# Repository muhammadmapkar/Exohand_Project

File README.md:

# ExoHand

EMG-controlled assistive robotic hand. Built for ECTE351 by Team Orvyn (Group 19).

## Overview

ExoHand reads surface EMG (sEMG) from the forearm, classifies the muscle activity into a hand gesture, and drives four servo-actuated fingers to match. The current system recognizes `rest`, `fist`, and individual-finger gestures (`pinky&ring`, `middle`, `index`, `thumb`), running the trained classifier directly on the microcontroller. VR integration is planned; not yet in this codebase. — see `docs/architecture.md`. Runs the trained classifier on-device (no PC needed for inference).

## EMG-control concept

1. Sample raw EMG at 1 kHz from a single sensor channel.
2. Extract statistical features (MAV, RMS, variance, std dev, waveform length, zero-crossing rate, slope sign changes, skewness, kurtosis, IQR) over a rolling 30-sample window.
3. Classify the window with a Random Forest trained on EMG collected by the team (plus validation against the public NinaPro benchmark dataset).
4. Debounce the result (4 agreeing windows + 150ms hold) before committing to a new gesture.
5. Drive 4 servos through a PCA9685 to match the confirmed gesture, moving smoothly rather than snapping.

Full signal-flow diagram: `docs/architecture.md`.

## Hardware stack

- Teensy 4.0 — main MCU for EMG sampling, feature extraction, and on-device RF inference
- PCA9685 servo driver (I2C, 4 channels)
- MG996R servos (or equivalent)
- SEN0240 EMG sensor
- ESP32-C3, for live telemetry/graph relay (`firmware/current/esp32_bridge.ino` — self-hosted WiFi AP + WebSocket server)

## Repo layout

```
exohand/
├── firmware/        Teensy/ESP32 .ino code — current/ is what's in active use, archive/ is superseded versions
├── web/             static site + the FastAPI live dashboard
├── hardware/        KiCad schematics/PCB, BOM, perfboard build docs
├── signal-processing/  EMG filtering, feature extraction, trained model, datasets
├── docs/            build-log, architecture, decisions, posters
└── media/           screenshots, recordings, concept art
```

Nothing failed or superseded was deleted — old firmware versions, every dated PCB backup, duplicate dataset exports, and earlier notebook runs are all kept under the relevant `archive/` folders. See `docs/build-log.md` for the full story of what was tried and what changed.

## How to build / run

**Firmware:** open `firmware/current/teensy_final.ino` in Arduino IDE with Teensyduino (board: Teensy 4.0), plus the Adafruit PWM Servo Driver and Watchdog_t4 libraries. It includes `ai_classifier_model.h`, which is checked into `firmware/current/` and compiles as-is. To regenerate it from a retrained model, run `python3 signal-processing/export_model_to_header.py` (loads `ExoHand_RF_Model.joblib` + `ExoHand_Scaler.joblib`, writes the header back to `firmware/current/ai_classifier_model.h`).

**Signal processing / training:** `pip install -r signal-processing/requirements.txt`, then `signal-processing/ExoHand_EMG_Classifier_RF_V2.ipynb` to retrain, or `signal-processing/live_predict.py` to run live PC-side inference over serial.

**Live dashboard:** `web/dashboard/app.py` (FastAPI). Install `web/dashboard/requirements.txt`, run with `uvicorn app:app`, open the browser page it serves. Includes a `/api/demo` mode that fakes EMG data if no hardware is connected.

**Website:** `web/website.html` is the current main site (Live Rehab dashboard view, live EMG chart, camera-based sensor-placement assistant). `web/archive/ORVYNUpdated.html` is an earlier, less developed version.

**Hardware:** schematics and PCB in `hardware/schematics/`, BOM in `hardware/bom/`, perfboard wiring/assembly in `hardware/perfboard/`.

## Credit

Team Orvyn (Group 19). My role: led firmware (Teensy), EMG signal processing, hardware build. Data collection was team effort. Benchmark data from NinaPro.

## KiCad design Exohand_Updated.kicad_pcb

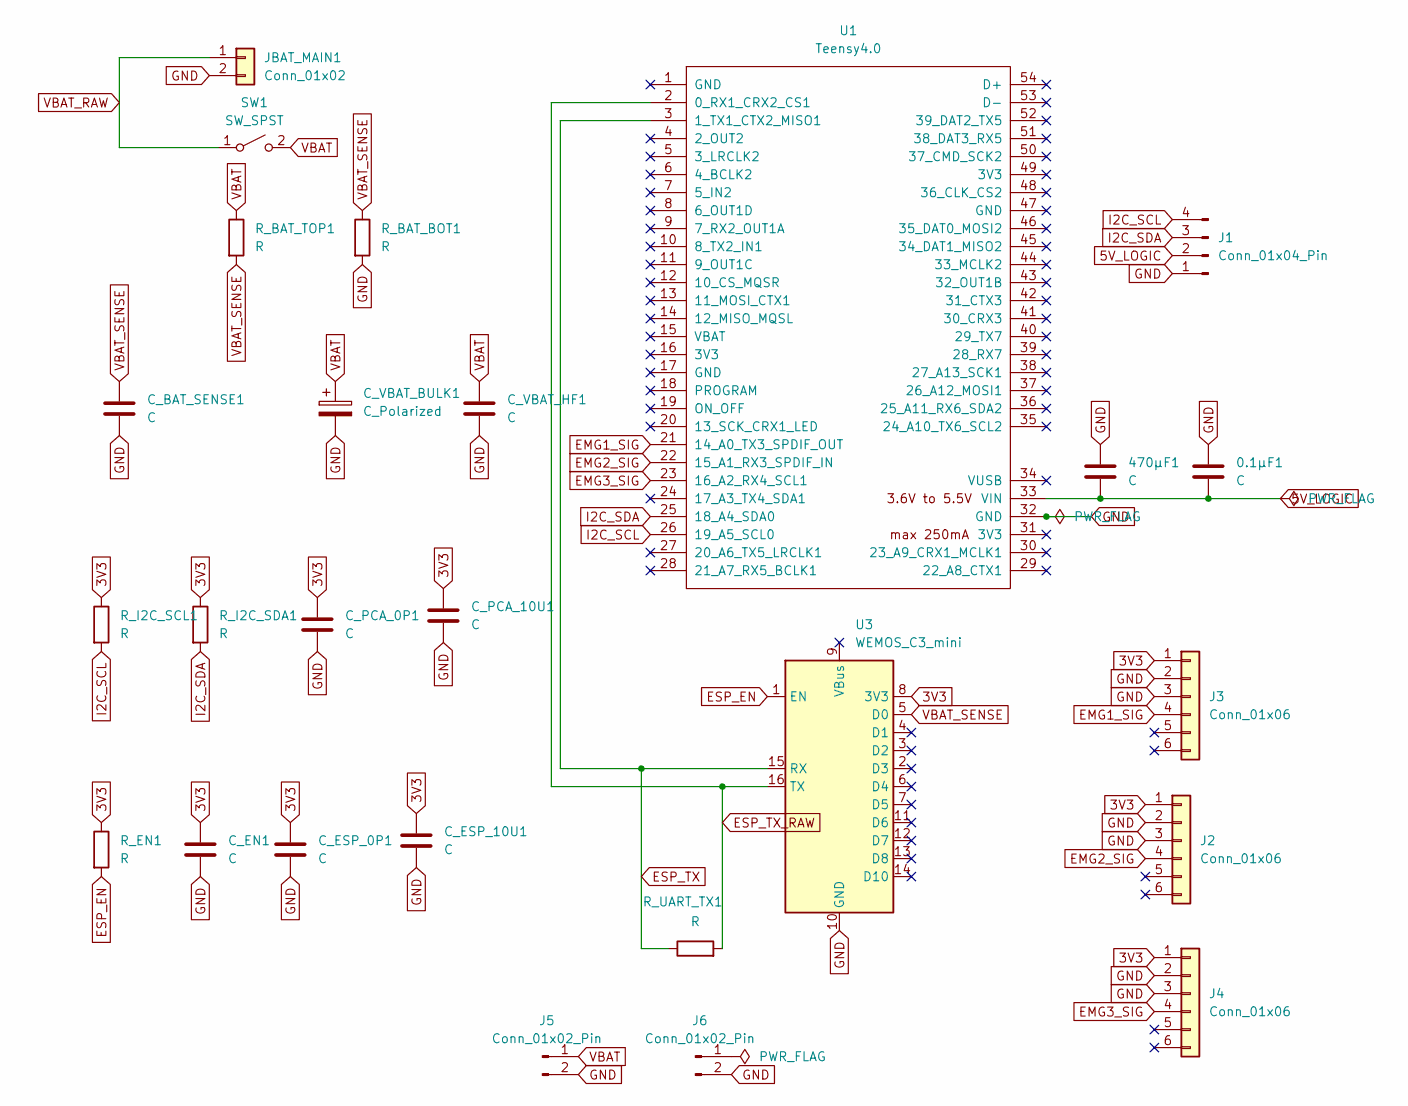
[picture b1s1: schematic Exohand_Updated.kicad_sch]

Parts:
0.1µF1, 470µF1: C; C_0805_2012Metric
C_BAT_SENSE1: C; C_0805_2012Metric
C_EN1: C; C_0805_2012Metric
C_ESP_0P1, C_ESP_10U1: C; C_0805_2012Metric
C_PCA_0P1, C_PCA_10U1: C; C_0805_2012Metric
C_VBAT_BULK1: C_Polarized; CP_Radial_D8.0mm_P3.50mm
C_VBAT_HF1: C; C_0805_2012Metric
J1: Conn_01x04_Pin; PinHeader_1x04_P2.54mm_Vertical_SMD_Pin1Left
J2, J3, J4: Conn_01x06; PinHeader_1x06_P2.54mm_Vertical_SMD_Pin1Left
J5, J6: Conn_01x02_Pin; PinHeader_1x02_P2.54mm_Vertical_SMD_Pin1Left
JBAT_MAIN1: Conn_01x02; AMASS_XT30UPB-F_1x02_P5.0mm_Vertical
R_BAT_BOT1: R; R_0805_2012Metric
R_BAT_TOP1: R; R_0805_2012Metric
R_EN1: R; R_0805_2012Metric
R_I2C_SCL1, R_I2C_SDA1: R; R_0805_2012Metric
R_UART_TX1: R; R_0805_2012Metric
SW1: SW_SPST; KCD1-101
U1: Teensy4.0; Teensy40
U3: WEMOS_C3_mini

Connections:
3V3: C_EN1.1, C_ESP_0P1.1, C_ESP_10U1.1, C_PCA_0P1.1, C_PCA_10U1.1, J2.1, J3.1, J4.1, R_EN1.1, R_I2C_SCL1.1, R_I2C_SDA1.1, U3.8 (3V3)
5V_LOGIC: 0.1µF1.2, 470µF1.2, J1.2, U1.33 (VIN)
EMG1_SIG: J3.4, U1.21 (14_A0_TX3_SPDIF_OUT)
EMG2_SIG: J2.4, U1.22 (15_A1_RX3_SPDIF_IN)
EMG3_SIG: J4.4, U1.23 (16_A2_RX4_SCL1)
ESP_EN: R_EN1.2, U3.1 (EN)
ESP_TX: R_UART_TX1.1, U1.3 (1_TX1_CTX2_MISO1), U3.15 (RX)
ESP_TX_RAW: R_UART_TX1.2, U1.2 (0_RX1_CRX2_CS1), U3.16 (TX)
GND: 0.1µF1.1, 470µF1.1, C_BAT_SENSE1.2, C_EN1.2, C_ESP_0P1.2, C_ESP_10U1.2, C_PCA_0P1.2, C_PCA_10U1.2, C_VBAT_BULK1.2, C_VBAT_HF1.2, J1.1, J2.2, J2.3, J3.2, J3.3, J4.2, J4.3, J5.2, J6.2, JBAT_MAIN1.2, R_BAT_BOT1.2, U1.32 (GND), U3.10 (GND)
I2C_SCL: J1.4, R_I2C_SCL1.2, U1.26 (19_A5_SCL0)
I2C_SDA: J1.3, R_I2C_SDA1.2, U1.25 (18_A4_SDA0)
VBAT: C_VBAT_BULK1.1, C_VBAT_HF1.1, J5.1, R_BAT_TOP1.1, SW1.2 (B)
VBAT_RAW: JBAT_MAIN1.1, SW1.1 (A)
VBAT_SENSE: C_BAT_SENSE1.1, R_BAT_BOT1.1, R_BAT_TOP1.2, U3.5 (D0)

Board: 2 copper layers, 26 parts (0 on the bottom side), 14 nets, no tracks yet.

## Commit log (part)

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2026-04-21 Initialize README.md with project details
    Added detailed project overview, features, architecture, hardware components, signal processing pipeline, software stack, and other relevant sections.
2026-04-21 Delete License section from README
    Removed License section from README.
2026-06-18 Add AI Classifier: RF model, scaler, live prediction script, and Live Dashboard web app
    - ExoHand_RF_Model.joblib: Trained Random Forest gesture classifier
    - ExoHand_Scaler.joblib: EMG input scaler
    - live_predict.py: Terminal-based live EMG prediction script
    - requirements.txt: Python dependencies
    - ExoHand_Live_Dashboard/: FastAPI real-time browser dashboard
    - WebSocket streaming, Chart.js EMG graph, gesture history
2026-06-20 Fix Web Serial parser for Teensy raw samples and add ESP32 bridge code
2026-06-24 chore: remove old AI_Classifier flat-layout paths (superseded by exohand/ structure)
2026-06-24 feat(web): add static site and FastAPI live EMG dashboard
2026-06-24 feat(firmware): add current + archived Teensy/ESP32 firmware sketches
2026-06-24 feat(hardware): add KiCad schematics/PCB (+20 backups), BOM, perfboard docs
2026-06-24 feat(signal-processing): add filtering pipeline, RF classifier, model artifacts, datasets (benchmark/collected/processed)
2026-06-24 docs: add README, build-log, architecture, decisions, posters, media
2026-06-24 feat: pull in firmware/web files from GitHub history not present locally
    - teensy_final.ino supersedes ExoHand_Teensy.ino (watchdog, EEPROM, heartbeat)
    - esp32_bridge.ino: actual WiFi/WebSocket telemetry bridge (fills prior gap)
    - website.html supersedes ORVYNUpdated.html (Live Rehab view, live chart, FaceMesh placement assist)
    - exohand_demo.mp4 added to media/
    - docs corrected to remove now-stale 'ESP32 bridge not found' notes
2026-06-24 Generate missing ai_classifier_model.h from trained model
    - Add signal-processing/export_model_to_header.py: loads
    ExoHand_RF_Model.joblib + ExoHand_Scaler.joblib and exports the real
    trained Random Forest (200 trees, 23024 nodes, 10 features, 6 classes)
    and the real EMG scaler (mean/scale) as plain C arrays + a standalone
    tree-walk inference helper. No invented values -- everything is read
    directly from the joblib files, matching the feature order/scaling
2026-06-24 Standardize on Teensy 4.0 everywhere, resolve 4.0/4.1 contradiction
    Project hardware is Teensy 4.0 (matches the firmware's own header comments
    and the schematics). Removed every '4.1' reference that had crept into the
    dashboard/web side:
    - README.md, docs/architecture.md: state Teensy 4.0 plainly, no hedging.
    - web/dashboard/app.py: docstring corrected; fixed the always-'Teensy 4.1'
    port-label ternary (both branches returned the same string -- a no-op
